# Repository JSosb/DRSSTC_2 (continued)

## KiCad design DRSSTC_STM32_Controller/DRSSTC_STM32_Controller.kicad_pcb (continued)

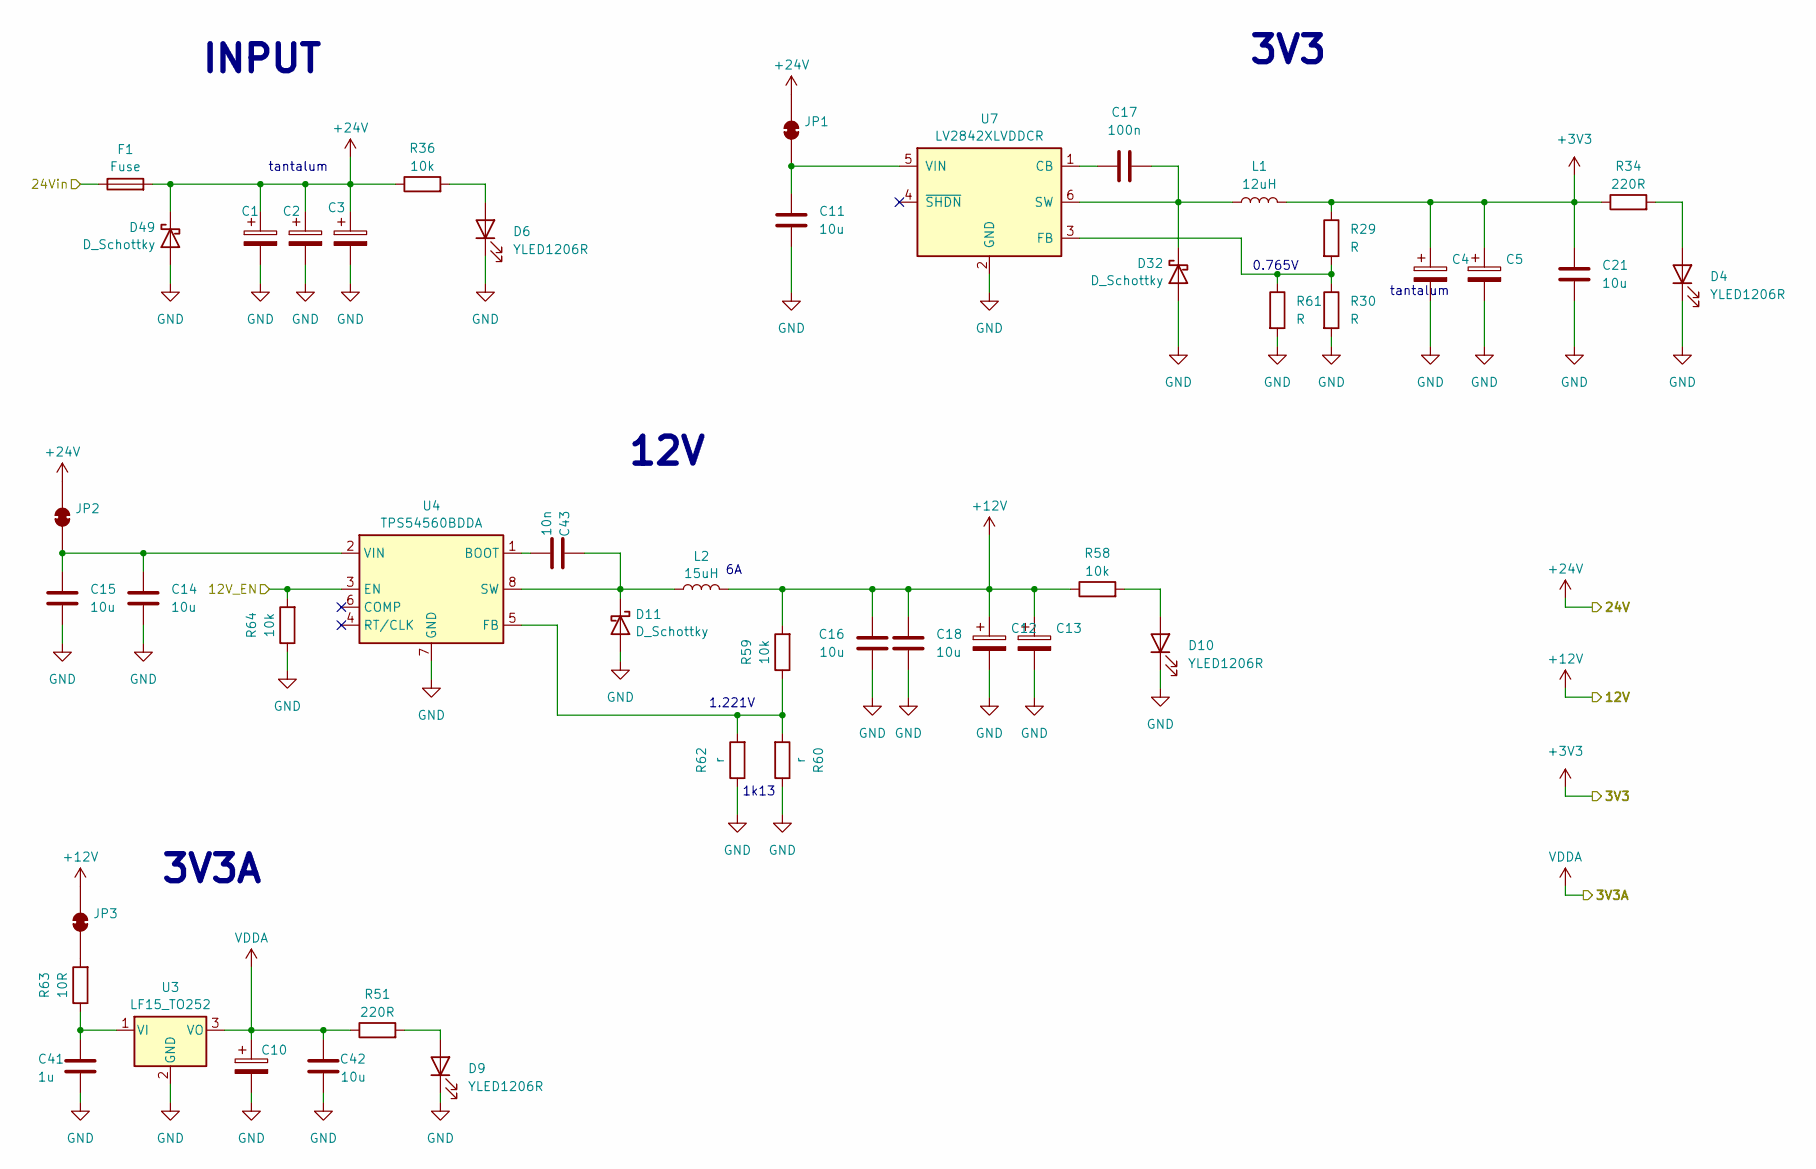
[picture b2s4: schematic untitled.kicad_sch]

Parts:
C1, C2, C3, C12, C13: C_Polarized; CP_Elec_10x10
C4, C5, C10: C_Polarized; CP_EIA-3528-12_Kemet-T
C11, C14, C15, C16, C18, C21, C42: 10u; C_0805_2012Metric
C17: 100n; C_0603_1608Metric
C41: 1u; C_0603_1608Metric
C43: 10n; C_0603_1608Metric
D4, D6, D9, D10: YLED1206R; LED_1206_3216Metric
D11, D32, D49: D_Schottky; D_SOD-128
F1: Fuse; Fuse_2512_6332Metric
JP1, JP2, JP3: SolderJumper_2_Bridged; SolderJumper-2_P1.3mm_Bridged2Bar_RoundedPad1.0x1.5mm
L1: 12uH; L_Coilcraft_XAL6020-XXX
L2: 15uH; L_10.4x10.4_H4.8
R29, R30, R61: R; R_0603_1608Metric
R34, R51: 220R; R_0805_2012Metric
R36, R58: 10k; R_0805_2012Metric
R59, R64: 10k; R_0603_1608Metric
R60, R62: r; R_0603_1608Metric
R63: 10R; R_0805_2012Metric
U3: LF15_TO252; TO-252-3_TabPin2
U4: TPS54560BDDA; Texas_R-PDSO-G8_EP2.95x4.9mm_Mask2.4x3.1mm_ThermalVias
U7: LV2842XLVDDCR; SOT-23-6

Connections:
+3V3: C4.1, C5.1, C21.1, L1.2, R29.1, R34.1; also elsewhere on the board
+12V: C12.1, C13.1, C16.1, C18.1, JP3.2 (B), L2.2, R58.1, R59.2; also elsewhere on the board
+24V: C1.1, C2.1, C3.1, D49.1 (K), F1.2, JP1.2 (B), JP2.2 (B), R36.1; also elsewhere on the board
/MCU and comms/12V_EN: R64.2, U4.3 (EN); also elsewhere on the board
/PSU/24Vin: F1.1; also elsewhere on the board
GND: C1.2, C2.2, C3.2, C4.2, C5.2, C10.2, C11.2, C12.2, C13.2, C14.2, C15.2, C16.2, C18.2, C21.2, C41.2, C42.2, D4.1 (K), D6.1 (K), D9.1 (K), D10.1 (K), D11.2 (A), D32.2 (A), D49.2 (A), R30.2, R60.1, R61.2, R62.1, R64.1, U3.2 (GND), U4.7 (GND), U4.9 (GND), U7.2 (GND); also elsewhere on the board
unnamed: D4.2 (A), R34.2
unnamed: D6.2 (A), R36.2
unnamed: D9.2 (A), R51.2
unnamed: D10.2 (A), R58.2
unnamed: C43.1, D11.1 (K), L2.1, U4.8 (SW)
unnamed: C17.2, D32.1 (K), L1.1, U7.6 (SW)
unnamed: C11.1, JP1.1 (A), U7.5 (VIN)
unnamed: C14.1, C15.1, JP2.1 (A), U4.2 (VIN)
unnamed: JP3.1 (A), R63.2
unnamed: C41.1, R63.1, U3.1 (VI)
unnamed: C43.2, U4.1 (BOOT)
unnamed: R59.1, R60.2, R62.2, U4.5 (FB)
unnamed: C17.1, U7.1 (CB)
unnamed: R29.2, R30.1, R61.1, U7.3 (FB)
VDDA: C10.1, C42.1, R51.1, U3.3 (VO); also elsewhere on the board

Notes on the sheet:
tantalum
12V
INPUT
3V3
1k13
3V3A
1.221V
0.765V

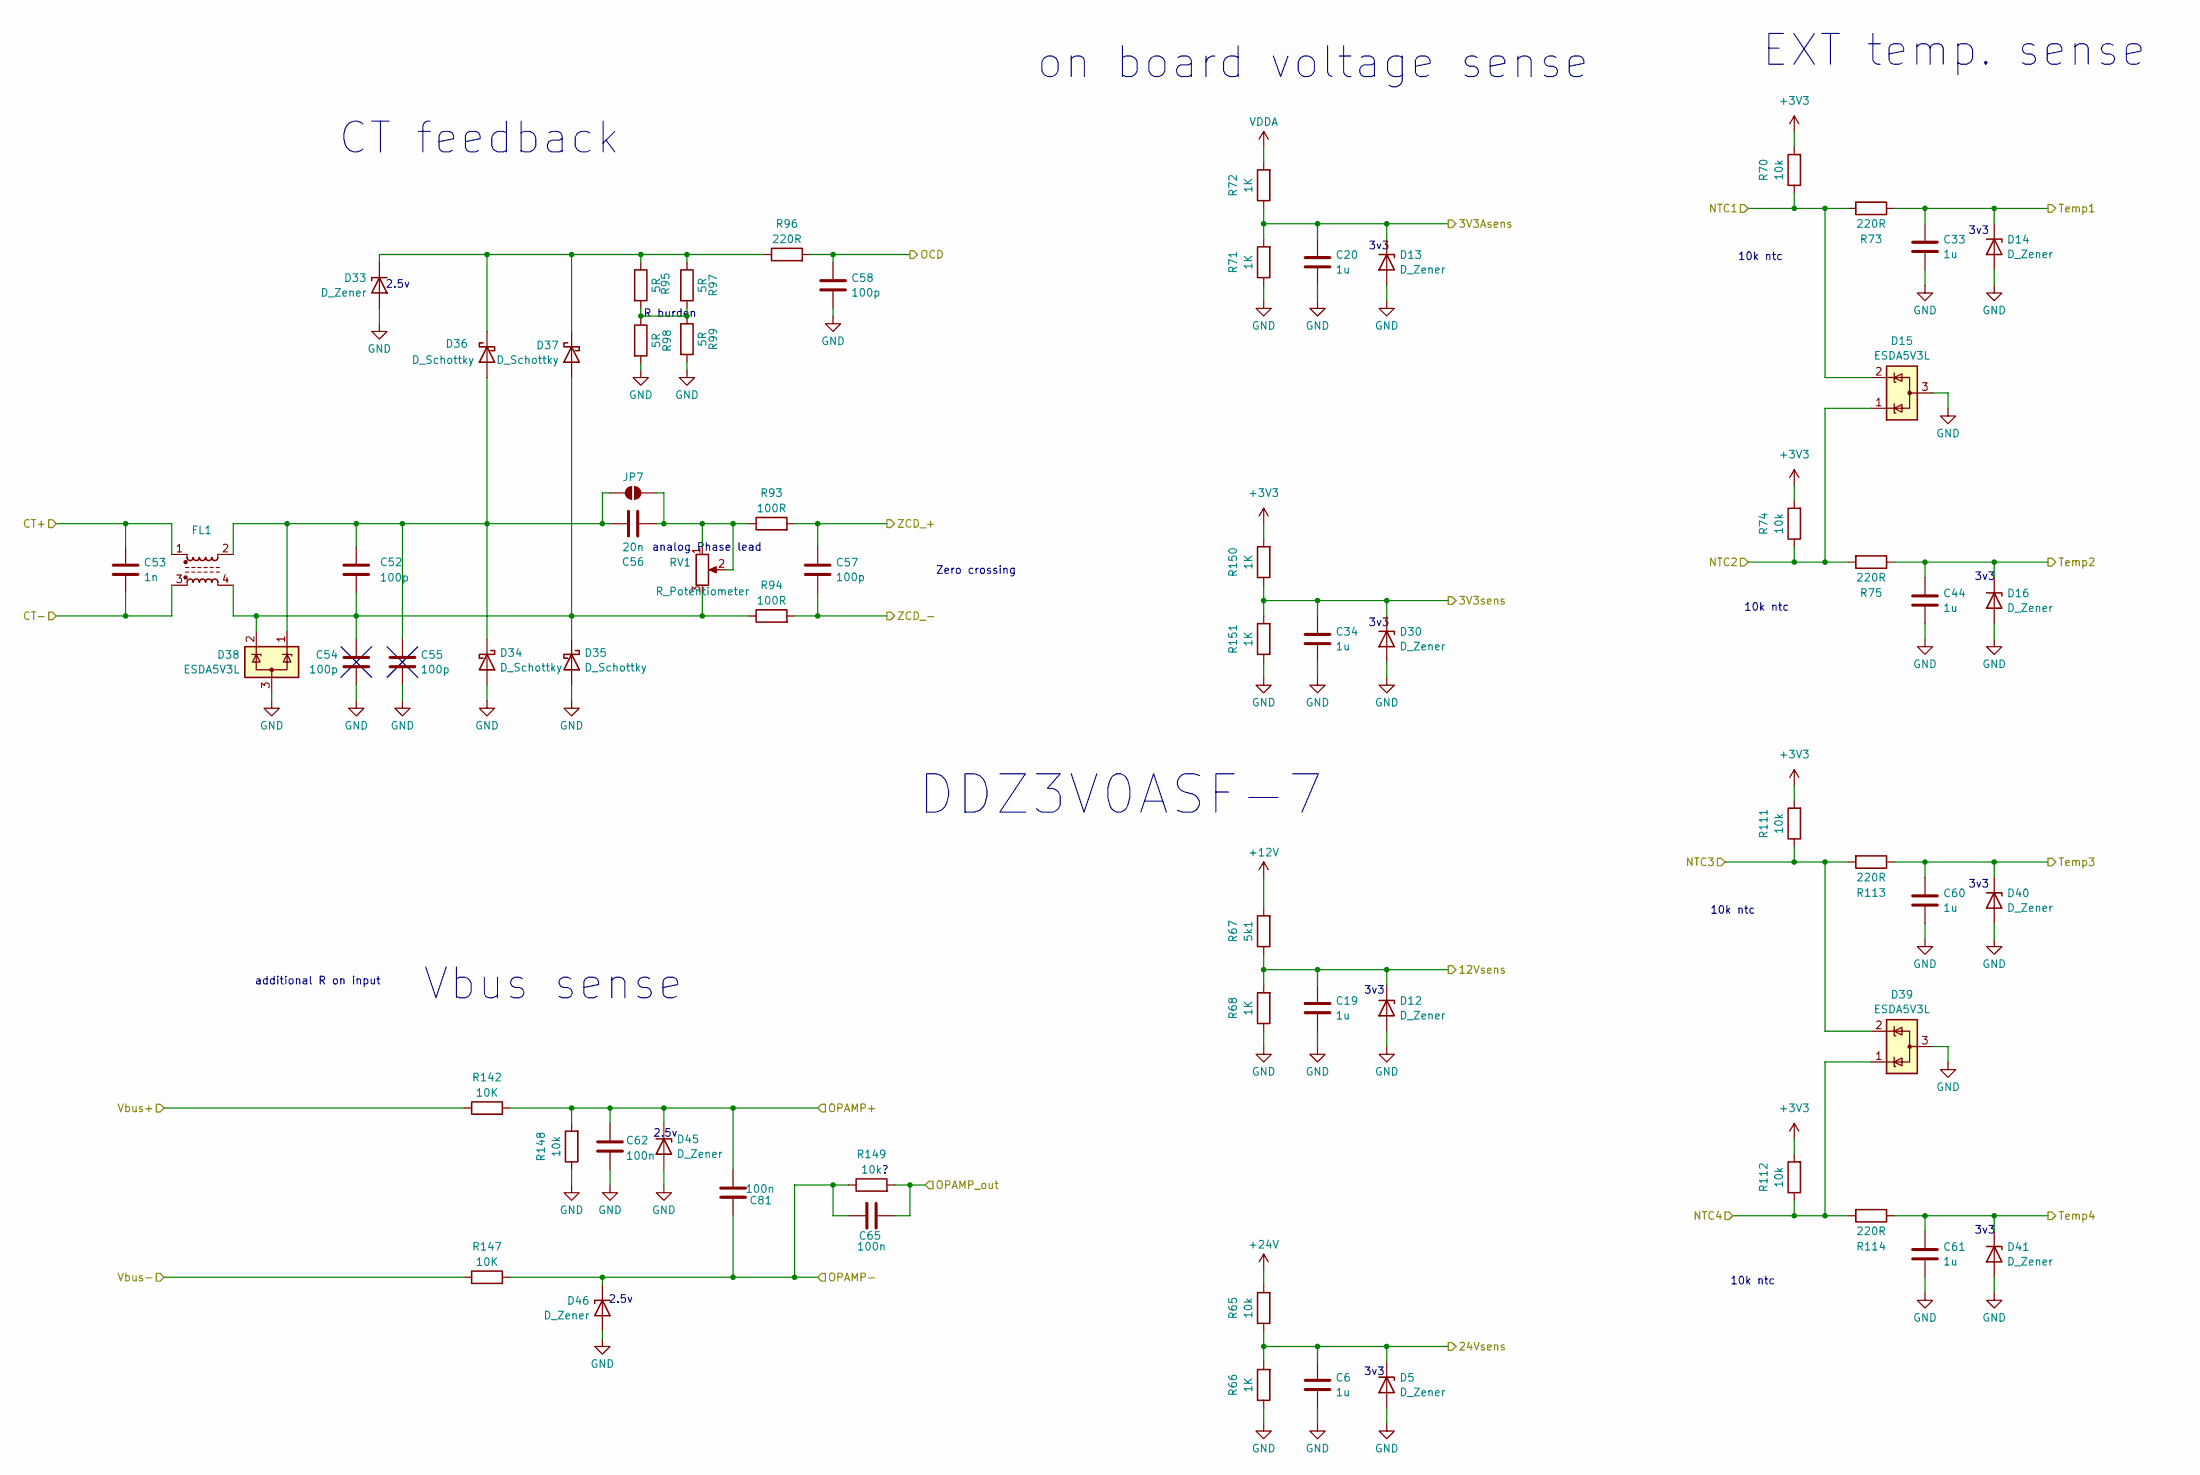
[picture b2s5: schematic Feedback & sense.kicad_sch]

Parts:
C6, C19, C20, C33, C34, C44, C60, C61: 1u; C_0603_1608Metric
C52, C54, C55, C57, C58: 100p; C_0603_1608Metric
C53: 1n; C_0603_1608Metric
C56: 20n; C_0603_1608Metric
C62, C65, C81: 100n; C_0603_1608Metric
D5, D12, D13, D14, D16, D30, D33, D40, D41, D45, D46: D_Zener; D_SOD-323F
D15, D38, D39: ESDA5V3L; SOT-23-3
D34, D35, D36, D37: D_Schottky; D_SOD-128
FL1: Choke_CommonMode_FerriteCore_1234; SW_MEC_5GSH9
JP7: SolderJumper_2_Open; SolderJumper-2_P1.3mm_Open_RoundedPad1.0x1.5mm
R65, R70, R74, R111, R112, R148, R149: 10k; R_0603_1608Metric
R66, R68, R71, R72, R150, R151: 1K; R_0603_1608Metric
R67: 5k1; R_0603_1608Metric
R73, R75, R96, R113, R114: 220R; R_0603_1608Metric
R93, R94: 100R; R_0603_1608Metric
R95, R97, R98, R99: 5R; R_1206_3216Metric
R142, R147: 10K; R_0603_1608Metric
RV1: R_Potentiometer; Potentiometer_ACP_CA6-H2,5_Horizontal

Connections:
+3V3: R70.2, R74.2, R111.2, R112.2, R150.2; also elsewhere on the board
+12V: R67.2; also elsewhere on the board
+24V: R65.2; also elsewhere on the board
/Feedback & sensing/3V3Asens: C20.1, D13.1 (K), R71.2, R72.1; also elsewhere on the board
/Feedback & sensing/3V3sens: C34.1, D30.1 (K), R150.1, R151.2; also elsewhere on the board
/Feedback & sensing/12Vsens: C19.1, D12.1 (K), R67.1, R68.2; also elsewhere on the board
/Feedback & sensing/24Vsens: C6.1, D5.1 (K), R65.1, R66.2; also elsewhere on the board
/Feedback & sensing/CT+: C53.1, FL1.1; also elsewhere on the board
/Feedback & sensing/CT-: C53.2, FL1.3; also elsewhere on the board
/Feedback & sensing/NTC1: D15.2 (K), R70.1, R73.2; also elsewhere on the board
/Feedback & sensing/NTC2: D15.1 (K), R74.1, R75.2; also elsewhere on the board
/Feedback & sensing/NTC3: D39.2 (K), R111.1, R113.2; also elsewhere on the board
/Feedback & sensing/NTC4: D39.1 (K), R112.1, R114.2; also elsewhere on the board
/Feedback & sensing/OCD: C58.1, R96.2; also elsewhere on the board
/Feedback & sensing/OPAMP+: C62.1, C81.2, D45.1 (K), R142.2, R148.2; also elsewhere on the board
/Feedback & sensing/OPAMP-: C65.1, C81.1, D46.1 (K), R147.2, R149.1; also elsewhere on the board
/Feedback & sensing/OPAMP_out: C65.2, R149.2; also elsewhere on the board
/Feedback & sensing/Temp1: C33.1, D14.1 (K), R73.1; also elsewhere on the board
/Feedback & sensing/Temp2: C44.1, D16.1 (K), R75.1; also elsewhere on the board
/Feedback & sensing/Temp3: C60.1, D40.1 (K), R113.1; also elsewhere on the board
/Feedback & sensing/Temp4: C61.1, D41.1 (K), R114.1; also elsewhere on the board
/Feedback & sensing/Vbus+: R142.1; also elsewhere on the board
/Feedback & sensing/Vbus-: R147.1; also elsewhere on the board
/Feedback & sensing/ZCD_+: C57.1, R93.2; also elsewhere on the board
/Feedback & sensing/ZCD_-: C57.2, R94.2; also elsewhere on the board
GND: C6.2, C19.2, C20.2, C33.2, C34.2, C44.2, C54.2, C55.2, C58.2, C60.2, C61.2, C62.2, D5.2 (A), D12.2 (A), D13.2 (A), D14.2 (A), D15.3 (A), D16.2 (A), D30.2 (A), D33.2 (A), D34.2 (A), D35.2 (A), D38.3 (A), D39.3 (A), D40.2 (A), D41.2 (A), D45.2 (A), D46.2 (A), R66.1, R68.1, R71.1, R98.2, R99.2, R148.1, R151.1; also elsewhere on the board
unnamed: D33.1 (K), D36.1 (K), D37.1 (K), R95.1, R96.1, R97.1
unnamed: C52.1, C55.1, C56.1, D34.1 (K), D36.2 (A), D38.1 (K), FL1.2, JP7.2 (B)
unnamed: C52.2, C54.1, D35.1 (K), D37.2 (A), D38.2 (K), FL1.4, R94.1, RV1.3
unnamed: C56.2, JP7.1 (A), R93.1, RV1.1, RV1.2
unnamed: R95.2, R97.2, R98.1, R99.1
VDDA: R72.2; also elsewhere on the board

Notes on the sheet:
10k ntc
R burden
3v3
Vbus sense
CT feedback
Zero crossing
2.5v
DDZ3V0ASF-7
analog Phase lead
on board voltage sense
additional R on input
EXT temp. sense

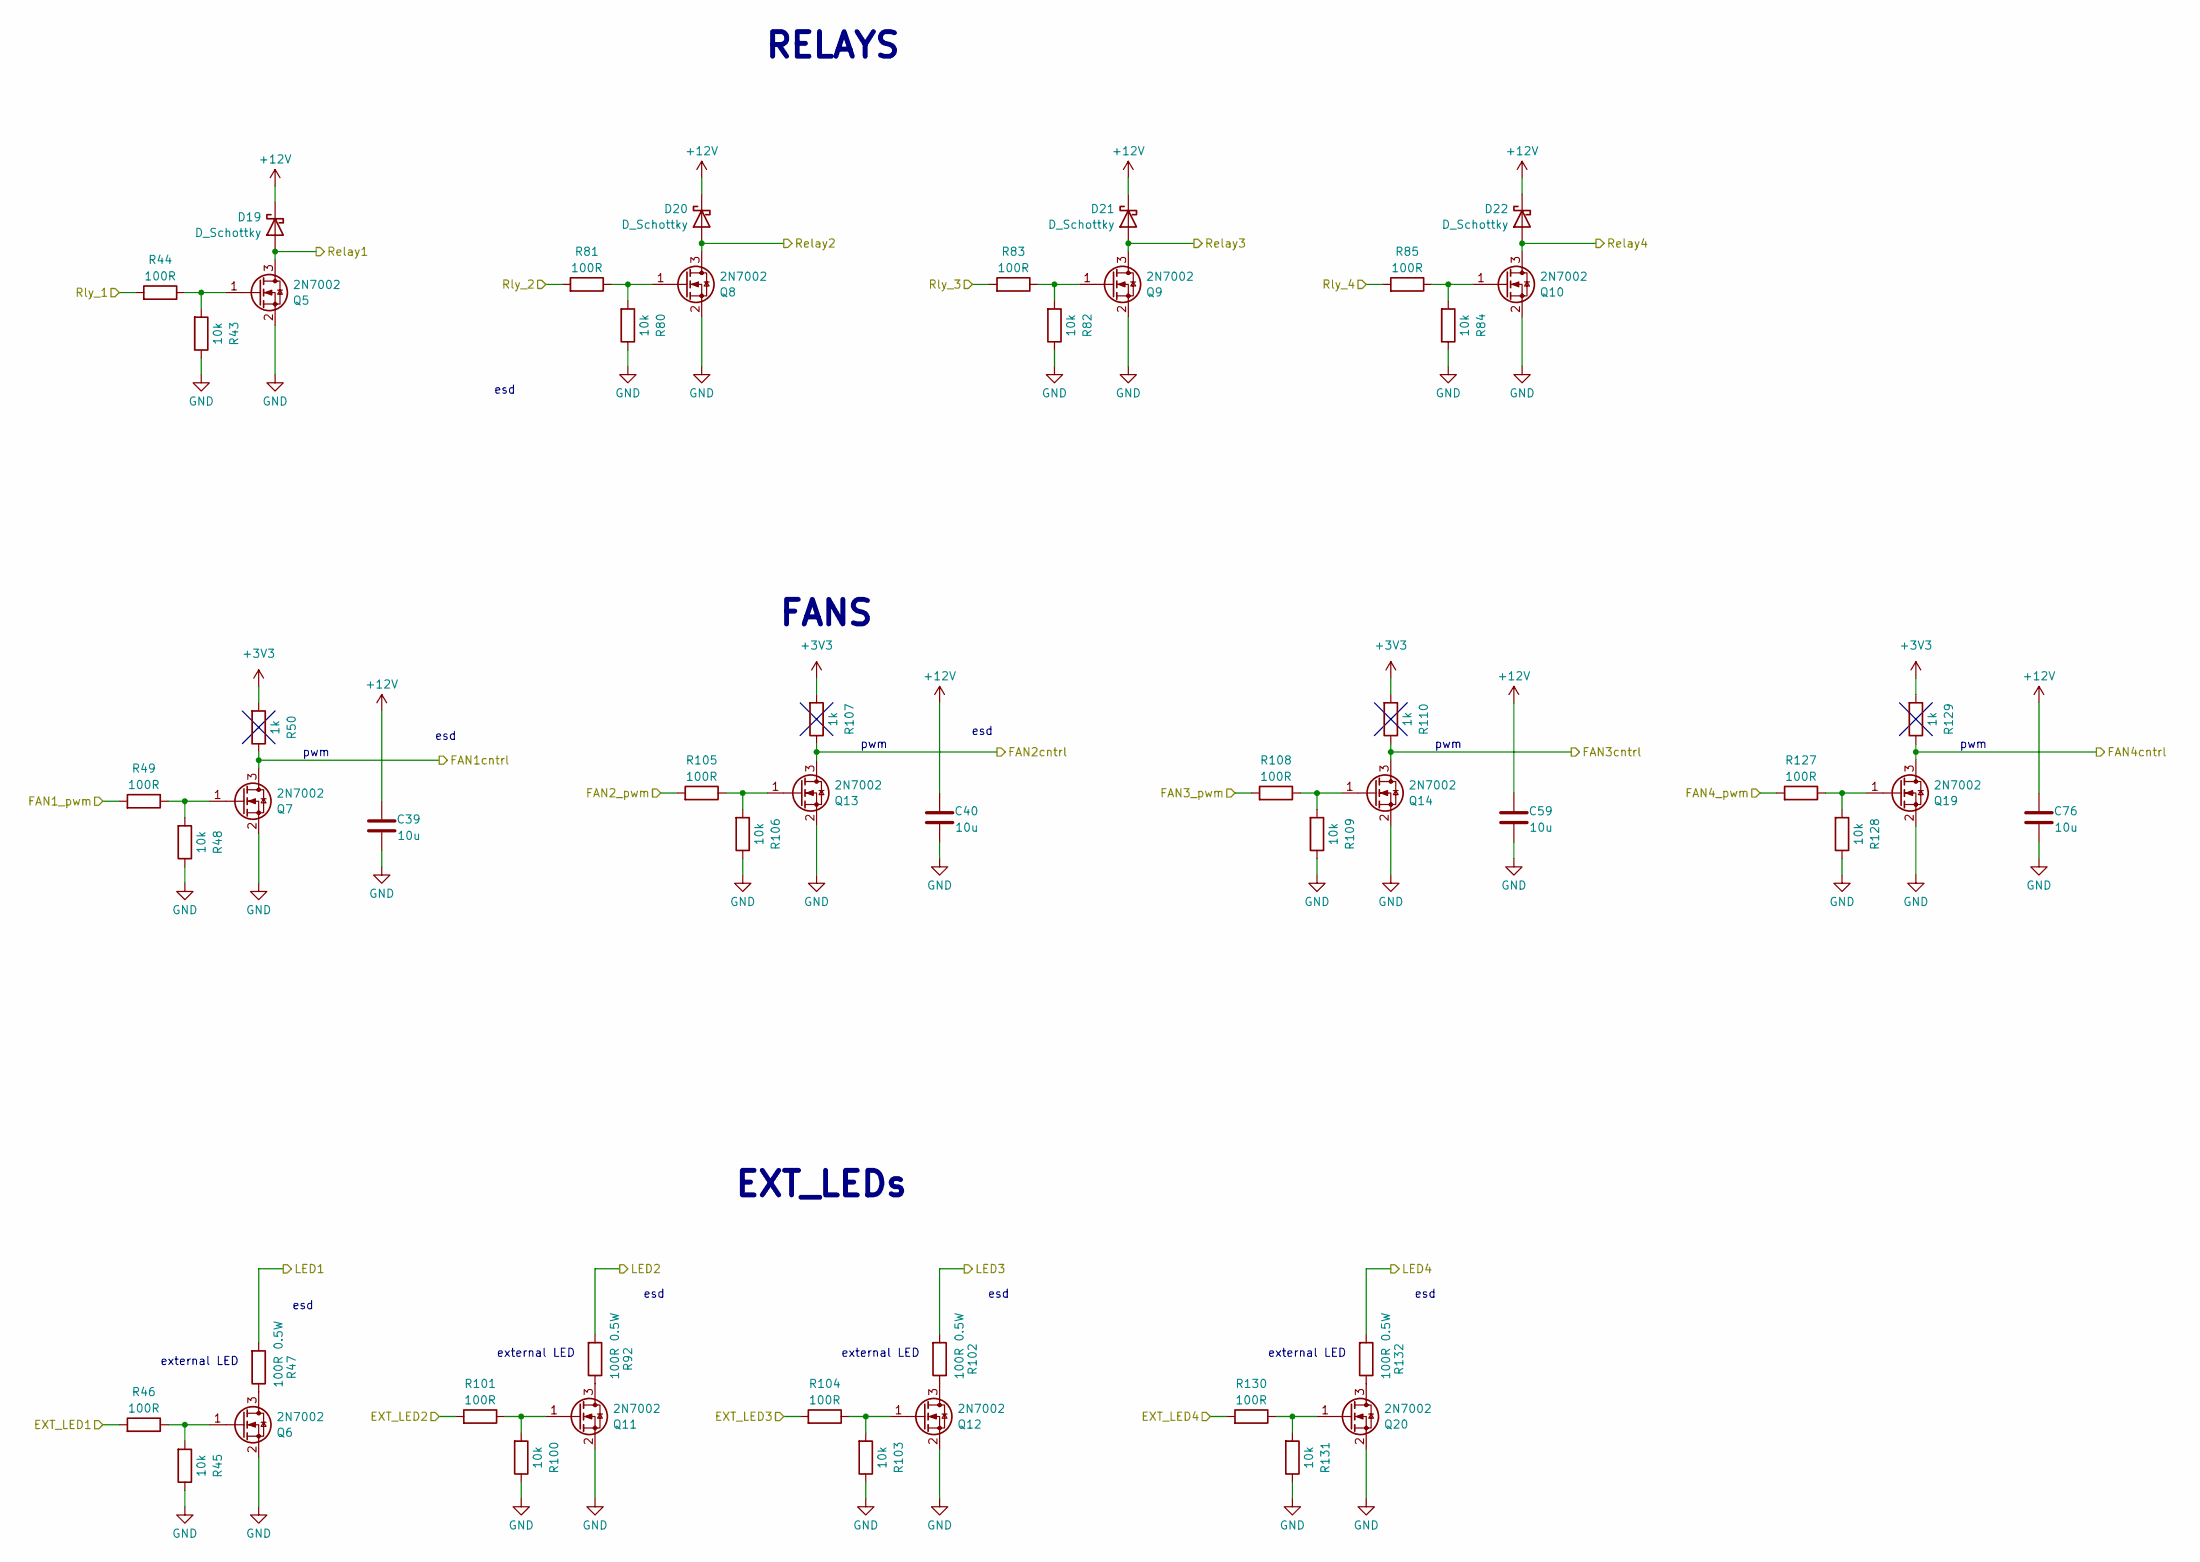
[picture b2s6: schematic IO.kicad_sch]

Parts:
C39, C40, C59, C76: 10u; C_0805_2012Metric
D19, D20, D21, D22: D_Schottky; D_SOD-128
Q5, Q6, Q7, Q8, Q9, Q10, Q11, Q12, Q13, Q14, Q19, Q20: 2N7002; SOT-23
R43, R45, R48, R80, R82, R84, R100, R103, R106, R109, R128, R131: 10k; R_0603_1608Metric
R44, R46, R49, R81, R83, R85, R101, R104, R105, R108, R127, R130: 100R; R_0603_1608Metric
R47, R92, R102, R132: 100R 0.5W; R_2512_6332Metric
R50, R107, R110, R129: 1k; R_0603_1608Metric

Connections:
+3V3: R50.2, R107.2, R110.2, R129.2; also elsewhere on the board
+12V: C39.1, C40.1, C59.1, C76.1, D19.1 (K), D20.1 (K), D21.1 (K), D22.1 (K); also elsewhere on the board
/MCU and comms/EXT_LED1: R46.2; also elsewhere on the board
/MCU and comms/EXT_LED2: R101.2; also elsewhere on the board
/MCU and comms/EXT_LED3: R104.2; also elsewhere on the board
/MCU and comms/EXT_LED4: R130.2; also elsewhere on the board
/MCU and comms/FAN1_pwm: R49.2; also elsewhere on the board
/MCU and comms/FAN2_pwm: R105.2; also elsewhere on the board
/MCU and comms/FAN3_pwm: R108.2; also elsewhere on the board
/MCU and comms/FAN4_pwm: R127.2; also elsewhere on the board
/MCU and comms/Rly_1: R44.2; also elsewhere on the board
/MCU and comms/Rly_2: R81.2; also elsewhere on the board
/MCU and comms/Rly_3: R83.2; also elsewhere on the board
/MCU and comms/Rly_4: R85.2; also elsewhere on the board
/power IO/FAN1cntrl: Q7.3 (D), R50.1; also elsewhere on the board
/power IO/FAN2cntrl: Q13.3 (D), R107.1; also elsewhere on the board
/power IO/FAN3cntrl: Q14.3 (D), R110.1; also elsewhere on the board
/power IO/FAN4cntrl: Q19.3 (D), R129.1; also elsewhere on the board
/power IO/LED1: R47.2; also elsewhere on the board
/power IO/LED2: R92.2; also elsewhere on the board
/power IO/LED3: R102.2; also elsewhere on the board
/power IO/LED4: R132.2; also elsewhere on the board
/power IO/Relay1: D19.2 (A), Q5.3 (D); also elsewhere on the board
/power IO/Relay2: D20.2 (A), Q8.3 (D); also elsewhere on the board
/power IO/Relay3: D21.2 (A), Q9.3 (D); also elsewhere on the board
/power IO/Relay4: D22.2 (A), Q10.3 (D); also elsewhere on the board
GND: C39.2, C40.2, C59.2, C76.2, Q5.2 (S), Q6.2 (S), Q7.2 (S), Q8.2 (S), Q9.2 (S), Q10.2 (S), Q11.2 (S), Q12.2 (S), Q13.2 (S), Q14.2 (S), Q19.2 (S), Q20.2 (S), R43.1, R45.1, R48.1, R80.1, R82.1, R84.1, R100.1, R103.1, R106.1, R109.1, R128.1, R131.1; also elsewhere on the board
unnamed: Q5.1 (G), R43.2, R44.1
unnamed: Q6.3 (D), R47.1
unnamed: Q6.1 (G), R45.2, R46.1
unnamed: Q7.1 (G), R48.2, R49.1
unnamed: Q8.1 (G), R80.2, R81.1
unnamed: Q9.1 (G), R82.2, R83.1
unnamed: Q10.1 (G), R84.2, R85.1
unnamed: Q11.3 (D), R92.1
unnamed: Q11.1 (G), R100.2, R101.1
unnamed: Q12.3 (D), R102.1
unnamed: Q12.1 (G), R103.2, R104.1
unnamed: Q13.1 (G), R105.1, R106.2
unnamed: Q14.1 (G), R108.1, R109.2
unnamed: Q19.1 (G), R127.1, R128.2
unnamed: Q20.3 (D), R132.1
unnamed: Q20.1 (G), R130.1, R131.2

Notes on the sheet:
pwm
external LED
esd
FANS
EXT_LEDs
RELAYS

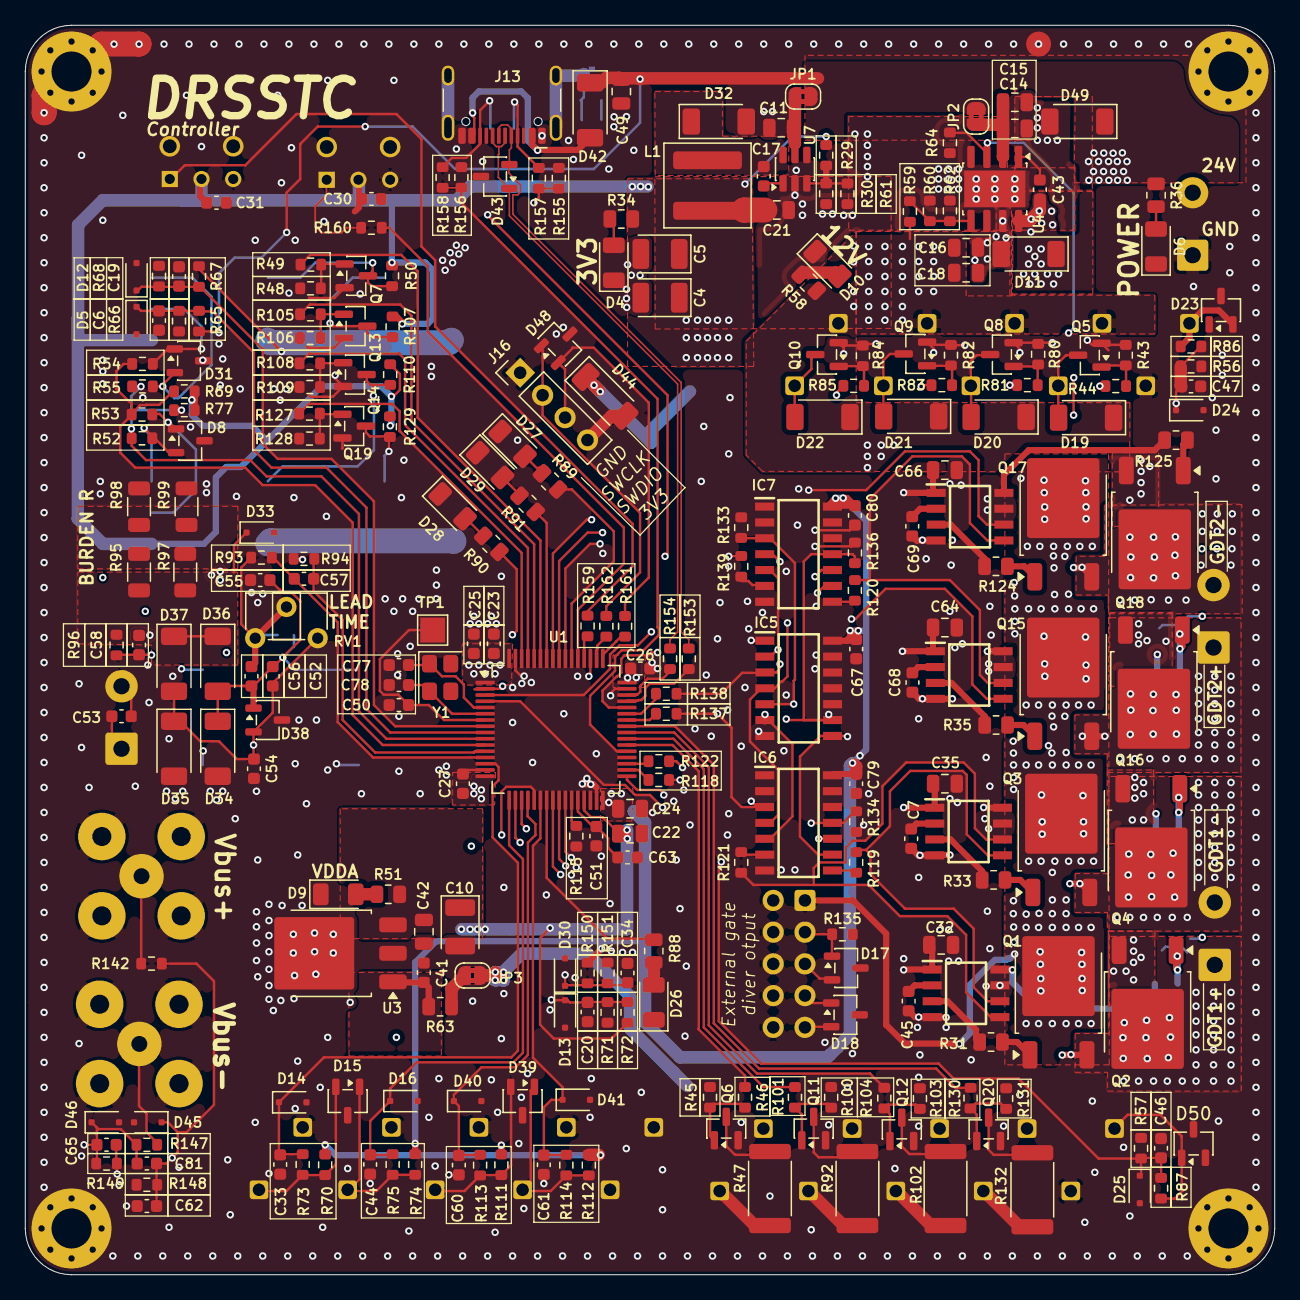
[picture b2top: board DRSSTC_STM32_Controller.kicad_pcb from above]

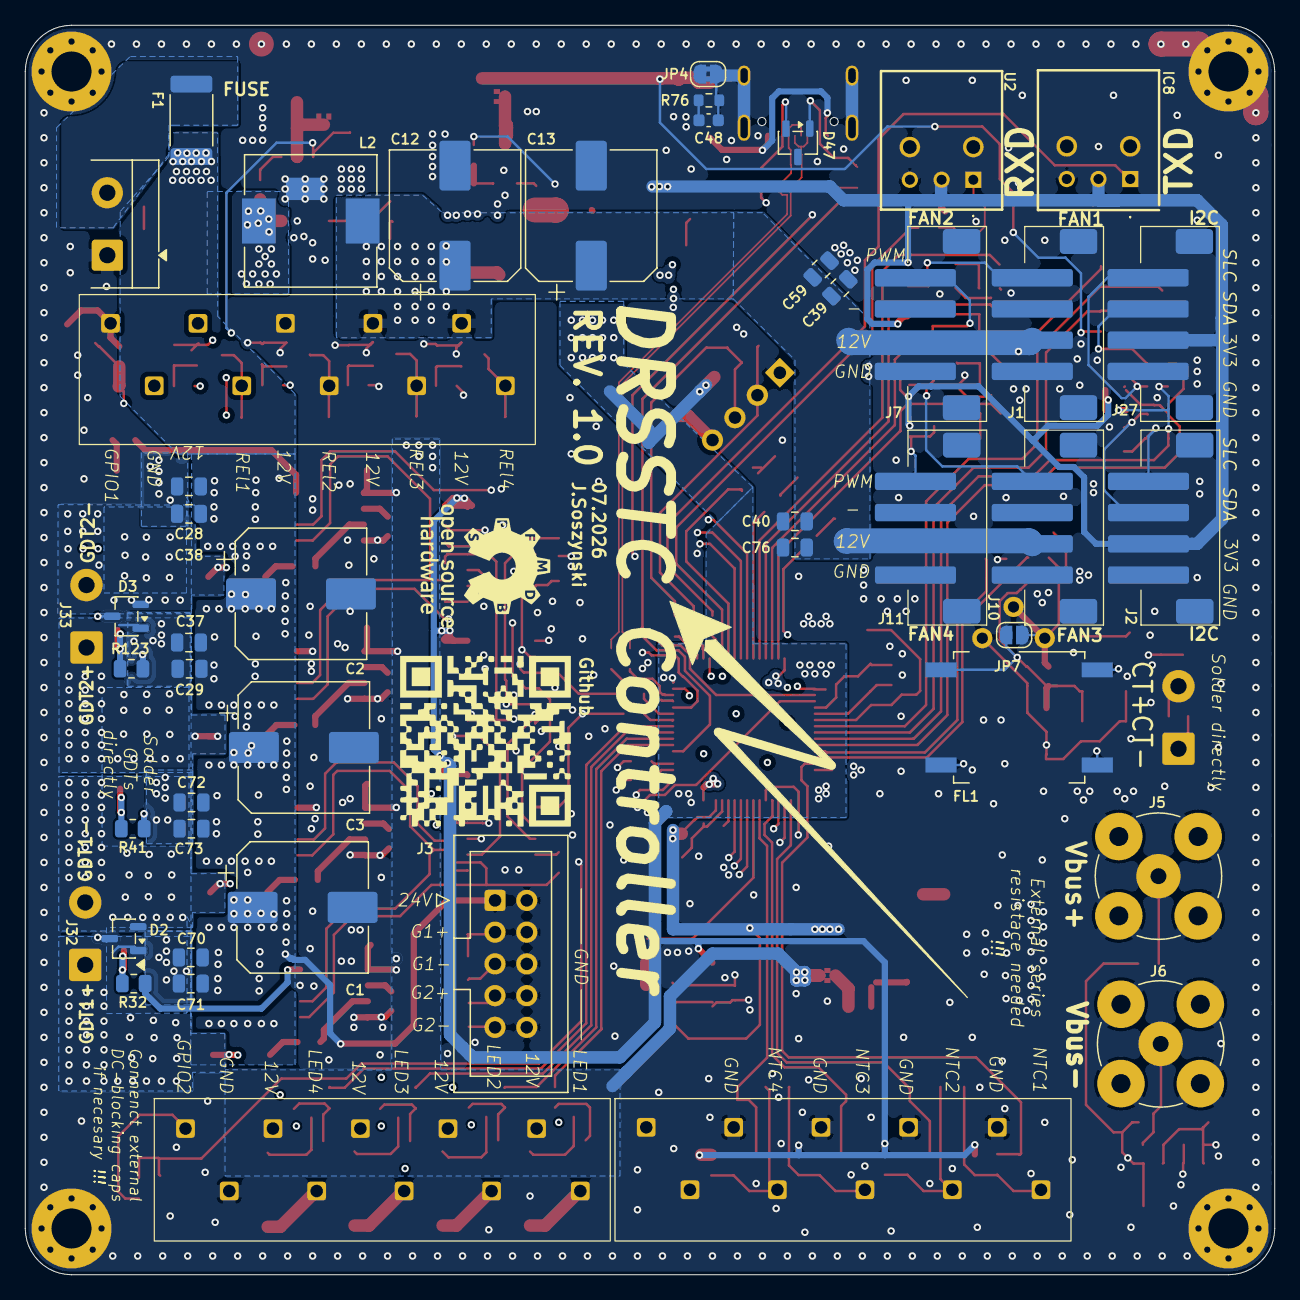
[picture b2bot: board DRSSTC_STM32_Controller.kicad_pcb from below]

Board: 4 copper layers, 100.0 x 100.0 mm, 308 parts (48 on the bottom side), 174 nets.

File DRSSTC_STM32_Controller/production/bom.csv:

Designator,Footprint,Quantity,Value,LCSC Part #
"C1, C12, C13, C2, C3",CP_Elec_10x10,5,C_Polarized,
"C10, C4, C5",CP_EIA-3528-12_Kemet-T,3,C_Polarized,
"C11, C14, C15, C16, C18, C21, C22, C24, C28, C29, C32, C35, C37, C38, C39, C40, C42, C49, C59, C64, C66, C70, C71, C72, C73, C76",0805,26,10u,
"C17, C45, C62, C65, C68, C69, C7, C81",0603,8,100n,
"C19, C20, C23, C25, C26, C27, C30, C31, C33, C34, C41, C44, C46, C47, C50, C51, C6, C60, C61, C63, C67, C79, C80",0603,23,1u,
"C43, C48",0603,2,10n,
"C52, C54, C55, C57, C58",0603,5,100p,
C53,0603,1,1n,
C56,0603,1,20n,
"C77, C78",0603,2,27p,
"D10, D26, D27, D28, D29, D4, D6, D9",1206,8,YLED1206R,
"D11, D19, D20, D21, D22, D32, D34, D35, D36, D37, D42, D44, D49",D_SOD-128,13,D_Schottky,
"D12, D13, D14, D16, D24, D25, D30, D33, D40, D41, D45, D46, D5",D_SOD-323F,13,D_Zener,
"D15, D17, D18, D2, D23, D3, D31, D38, D39, D43, D47, D48, D50, D8",SOT-23-3,14,ESDA5V3L,
F1,2512,1,Fuse,
FL1,SW_MEC_5GSH9,1,Choke_CommonMode_FerriteCore_1234,
"IC1, IC2, IC3, IC4",SOIC127P600X175-8N,4,UCC27282DR,
IC5,SOIC127P600X175-14N,1,SN74LVC14ADR,
"IC6, IC7",SOIC127P600X175-14N,2,SN74LVC11ADR,
IC8,PLT237T10WH,1,PLT237_T10WH,
"J1, J10, J11, J2, J27, J7",4PIN SMD 2.54,6,Conn_01x04,
"J12, J14, J17",terminal 10pin,3,Conn_01x10,
J13,USB_C_Receptacle_HCTL_HC-TYPE-C-16P-01A,1,USB_C_Receptacle_USB2.0_14P,
J16,PinHeader_1x04_P2.54mm_Vertical,1,Conn_01x04,
J3,IDC-Header_2x05_P2.54mm_Vertical,1,Conn_02x05_Odd_Even,
"J32, J33, J42",TerminalBlock_MetzConnect_Type094_RT03502HBLU_1x02_P5.00mm_Horizontal,3,Screw_Terminal_01x02,
J4,TerminalBlock_MetzConnect_Type055_RT01502HDWU_1x02_P5.00mm_Horizontal,1,Screw_Terminal_01x02,
"J5, J6",BNC_TEConnectivity_1478204_Vertical,2,Conn_Coaxial,
L1,L_Coilcraft_XAL6020-XXX,1,12uH,
L2,L_10.4x10.4_H4.8,1,15uH,
"Q1, Q15, Q16, Q17, Q18, Q2, Q3, Q4",TO-252-2,8,QM6006D,
"Q10, Q11, Q12, Q13, Q14, Q19, Q20, Q5, Q6, Q7, Q8, Q9",SOT-23,12,2N7002,
"R100, R103, R106, R109, R111, R112, R128, R131, R133, R134, R135, R136, R142, R147, R148, R149, R43, R45, R48, R56, R57, R59, R64, R65, R70, R74, R80, R82, R84",0603,29,10k,
"R101, R104, R105, R108, R118, R119, R120, R121, R122, R127, R130, R137, R138, R139, R157, R158, R44, R46, R49, R52, R53, R54, R55, R81, R83, R85, R93, R94",0603,28,100R,
"R102, R132, R47, R92",2512,4,100R 0.5W,
"R107, R110, R129, R150, R151, R50, R66, R68, R71, R72, R86, R87",0603,12,1k,
"R113, R114, R73, R75, R96",0603,5,220R,
R115,0603,1,0R,
"R123, R124, R125, R31, R32, R33, R35, R41, R63",0805,9,10R,
"R153, R154, R159, R160, R161, R162",0603,6,22R,
"R155, R156",0603,2,5.1k,
"R29, R30, R60, R61, R62",0603,5,R,
"R34, R51, R88, R89, R90, R91",0805,6,220R,
"R36, R58",0805,2,10k,
R67,0603,1,5k1,
"R69, R77",0603,2,4k7,
R76,0603,1,1M,
"R95, R97, R98, R99",1206,4,5R,
RV1,"Potentiometer_ACP_CA6-H2,5_Horizontal",1,R_Potentiometer,
TP1,TestPoint_Pad_2.0x2.0mm,1,nrst,
U1,LQFP-64_10x10mm_P0.5mm,1,STM32G474RETx,
U2,PLR237T10BK,1,PLR237_T10BK,
U3,TO-252-3_TabPin2,1,LF15_TO252,
U4,Texas_R-PDSO-G8_EP2.95x4.9mm_Mask2.4x3.1mm_ThermalVias,1,TPS54560BDDA,
U7,SOT-23-6,1,LV2842XLVDDCR,
Y1,Crystal_SMD_3225-4Pin_3.2x2.5mm,1,Crystal,
